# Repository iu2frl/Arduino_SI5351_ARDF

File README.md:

# Arduino_SI5351_ARDF
Remix of the Wobbit board by IARU R1, built at 9A22YOTA camp

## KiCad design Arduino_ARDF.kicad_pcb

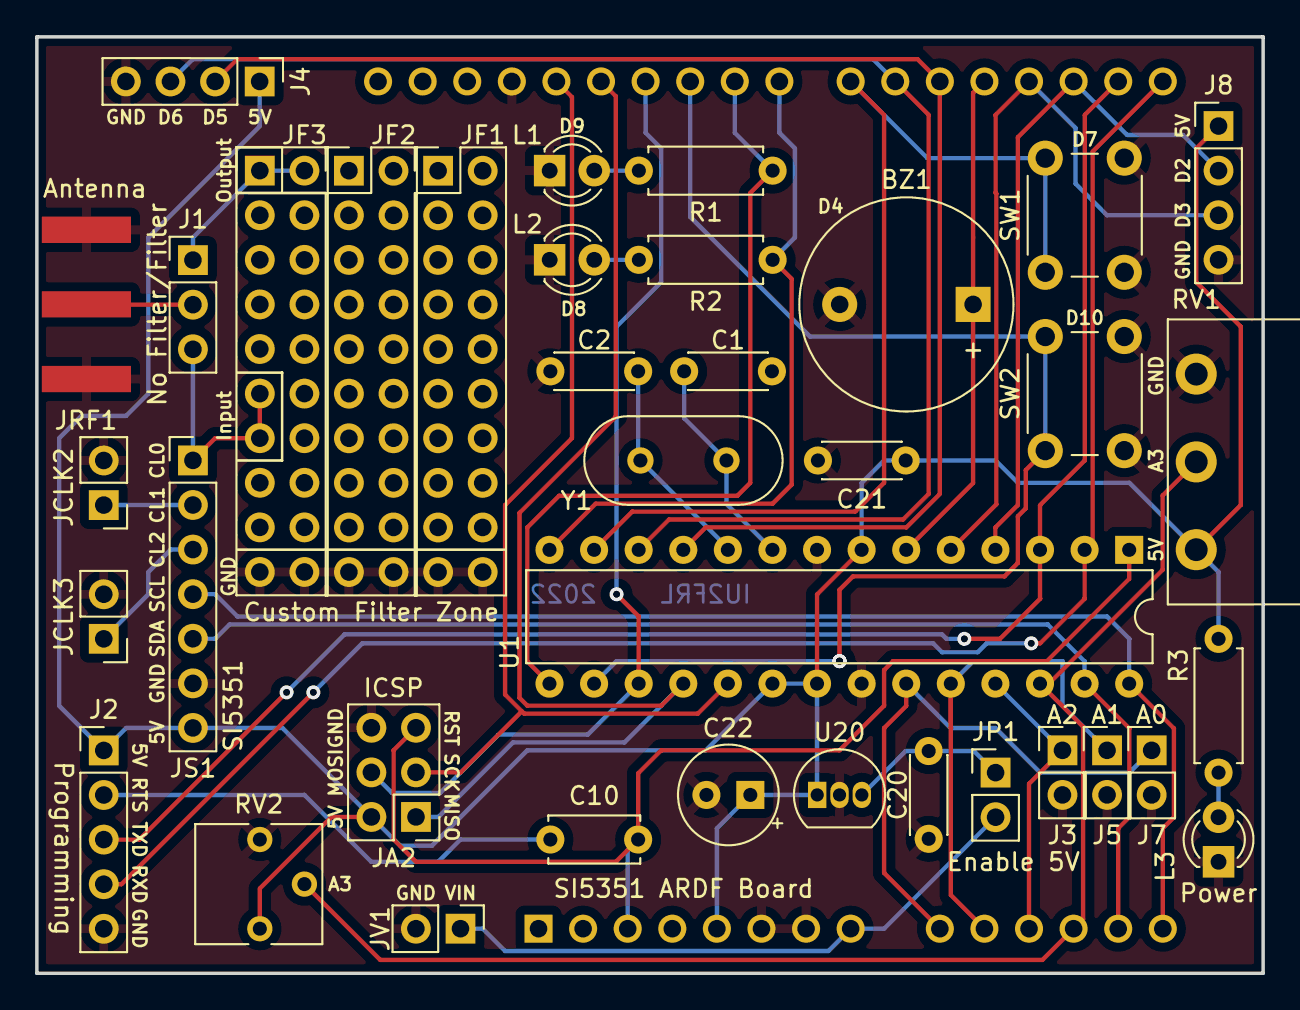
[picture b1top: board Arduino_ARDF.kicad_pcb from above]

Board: 2 copper layers, 69.8 x 53.3 mm, 38 parts (1 on the bottom side), 36 nets.

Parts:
BZ1: Buzzer; Buzzer_12x9.5RM7.6
C1, C2: 18p; C_Disc_D4.3mm_W1.9mm_P5.00mm
C10: 220n; C_Disc_D5.0mm_W2.5mm_P5.00mm
C20, C21: 100n; C_Disc_D4.3mm_W1.9mm_P5.00mm
C22: 47u; CP_Radial_Tantal_D5.5mm_P2.50mm
J1: Output Mode; PinHeader_1x03_P2.54mm_Vertical
J2: Programming; PinHeader_1x05_P2.54mm_Vertical
J3: Analog 2; PinHeader_1x02_P2.54mm_Vertical
J4: AUX2; PinHeader_1x04_P2.54mm_Vertical
J5: Analog 1; PinHeader_1x02_P2.54mm_Vertical
J7: Analog 0; PinHeader_1x02_P2.54mm_Vertical
J8: AUX1; PinHeader_1x04_P2.54mm_Vertical
JA1: Arduino_UNO_R3
JA2: ICSP; PinHeader_2x03_P2.54mm_Vertical
JCLK2: Clock 2; PinHeader_1x02_P2.54mm_Vertical
JCLK3: Clock 3; PinHeader_1x02_P2.54mm_Vertical
JF1: Filter 1; PinHeader_2x10_P2.54mm_Vertical
JF2: Filter 2; PinHeader_2x10_P2.54mm_Vertical
JF3: Filter 3; PinHeader_2x10_P2.54mm_Vertical
JP1: 5V EN; PinHeader_1x02_P2.54mm_Vertical
JRF1: OUT; SMA_Amphenol_132289_EdgeMount
JS1: SI5351 Board; PinHeader_1x07_P2.54mm_Vertical
JV1: Vin; PinHeader_1x02_P2.54mm_Vertical
L1, L2, L3: LED; LED_D3.0mm
R1, R2, R3: 470; R_Axial_DIN0207_L6.3mm_D2.5mm_P7.62mm_Horizontal
RV1: Potentiometer; Potentiometer_Piher_PC-16_Single_Horizontal
RV2: Potentiometer; Potentiometer_Vishay_T73YP_Vertical
SW1: Button 1; SW_PUSH_6mm
SW2: Button 2; SW_PUSH_6mm
U1: ATmega328-P; DIP-28_W7.62mm
U20: L78L05_TO92; TO-92_Inline
Y1: 16M; Crystal_HC18-U_Vertical

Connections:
+5V: C21.1, C22.1, J2.1, J4.1, J8.1, JA1.5 (+5V), JA2.2, JS1.7, R3.1, RV1.1, RV2.1, U1.7 (VCC), U1.20 (AVCC), U1.21 (AREF), U20.1 (VO)
A0: J7.1, JA1.9 (A0), U1.23 (PC0)
A1: J5.1, JA1.10 (A1), U1.24 (PC1)
A2: J3.1, JA1.11 (A2), U1.25 (PC2)
A3: JA1.12 (A3), RV1.2, RV2.2, U1.26 (PC3)
BUZ: BZ1.1 (-), JA1.19 (D4), U1.6 (PD4)
CLK0: J1.3, JF3.11, JF3.13, JS1.1
CLK1: JCLK2.1, JS1.2
CLK2: JCLK3.1, JS1.3
D2: J8.2, JA1.17 (D2), U1.4 (PD2)
D3: J8.3, JA1.18 (D3), U1.5 (PD3)
D5: J4.2, JA1.20 (D5), U1.11 (PD5)
D6: J4.3, JA1.21 (D6), U1.12 (PD6)
D7: JA1.22 (D7), SW1.1, U1.13 (PD7)
D10: JA1.25 (D10), SW2.1, U1.16 (PB2)
Filter: J1.1, JF3.1, JF3.2
GND: BZ1.2 (+), C1.1, C2.2, C20.2, C21.2, C22.2, J2.5, J3.2, J4.4, J5.2, J7.2, J8.4, JA1.6 (GND), JA1.7 (GND), JA1.29 (GND), JA2.6, JCLK2.2, JCLK3.2, JF1.19, JF1.20, JF2.19, JF2.20, JF3.19, JF3.20, JRF1.2 (Ext), JS1.6, JV1.2, L1.1 (K), L2.1 (K), L3.1 (K), RV1.3, RV2.3, SW1.2, SW2.2, U1.8 (GND), U1.22 (GND), U20.2 (GND)
LED1: JA1.24 (D9), R1.1, U1.15 (PB1)
LED2: JA1.23 (D8), R2.1, U1.14 (PB0)
MISO: JA1.27 (D12), JA2.1, U1.18 (PB4)
MOSI: JA1.26 (D11), JA2.4, U1.17 (PB3)
unnamed: C1.2, U1.9 (XTAL1/PB6), Y1.2
unnamed: C2.1, U1.10 (XTAL2/PB7), Y1.1
unnamed: C10.1, J2.2
unnamed: C20.1, JP1.1, U20.3 (VI)
unnamed: J1.2, JRF1.1 (In)
unnamed: L1.2 (A), R1.2
unnamed: L2.2 (A), R2.2
unnamed: L3.2 (A), R3.2
RST: C10.2, JA1.3 (~RESET), JA2.5, U1.1 (~RESET/PC6)
RXD: J2.4, JA1.15 (D0/RX), U1.2 (PD0)
SCK: JA1.28 (D13), JA2.3, U1.19 (PB5)
SCL: JA1.14 (SCL/A5), JS1.4, U1.28 (PC5)
SDA: JA1.13 (SDA/A4), JS1.5, U1.27 (PC4)
TXD: J2.3, JA1.16 (D1/TX), U1.3 (PD1)
VIN: JA1.8 (VIN), JP1.2, JV1.1

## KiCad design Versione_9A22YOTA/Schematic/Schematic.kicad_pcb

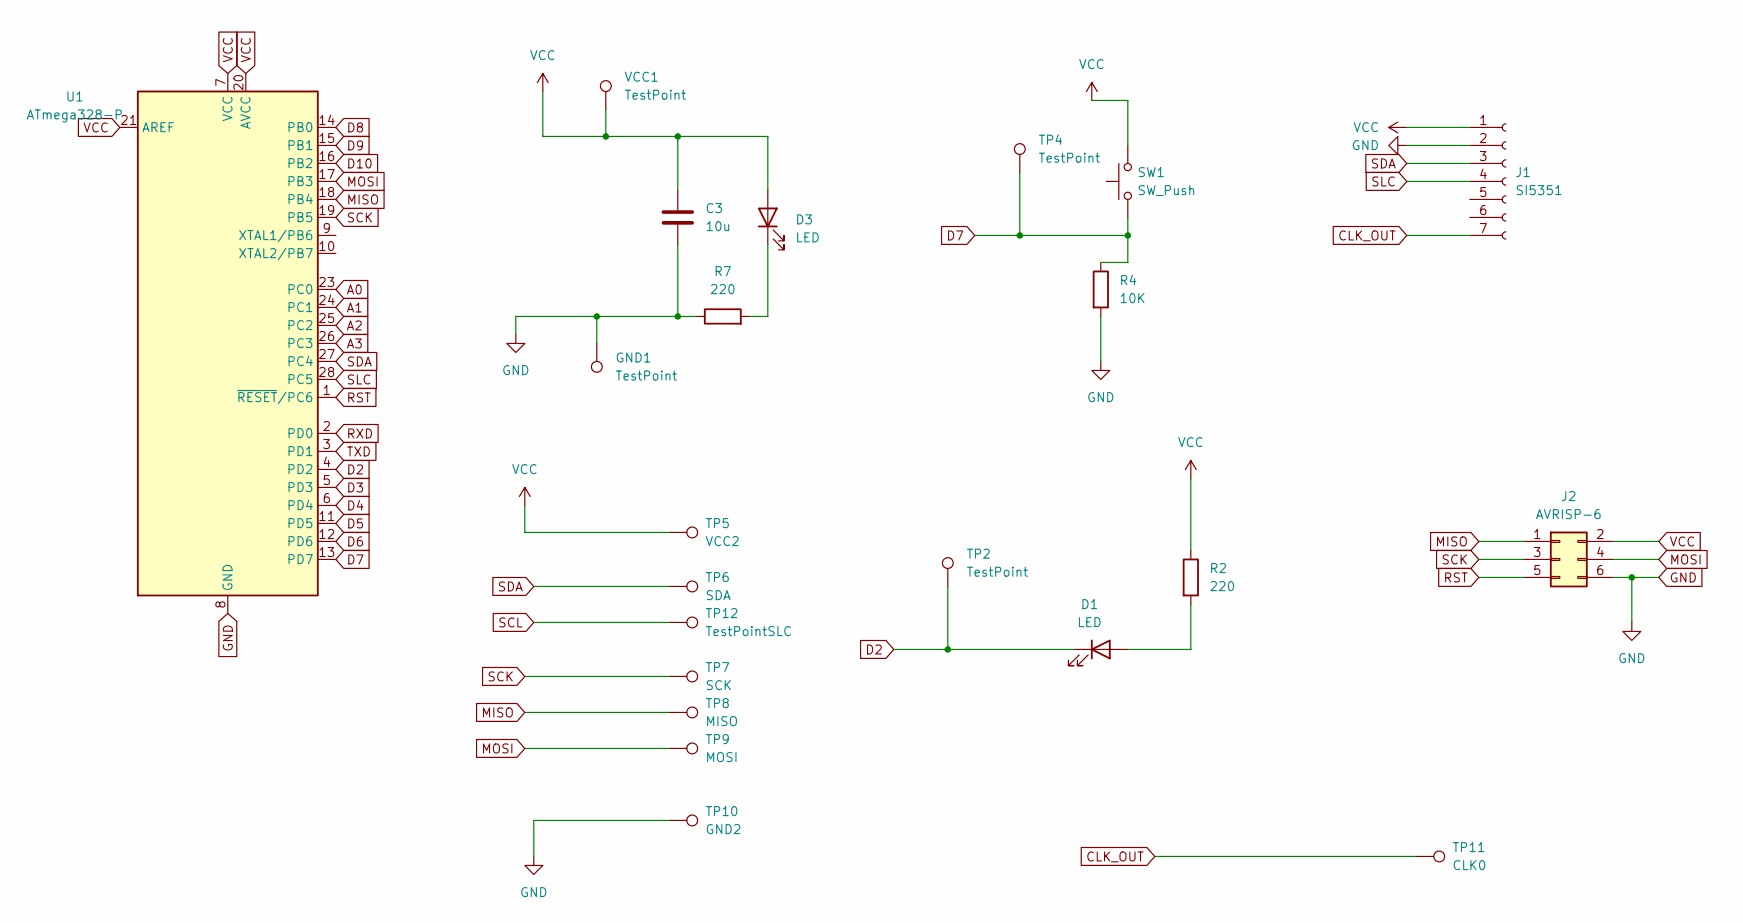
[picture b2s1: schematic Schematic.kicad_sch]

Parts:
C3: 10u; CP_Radial_D5.0mm_P2.00mm
D1, D3: LED; LED_D5.0mm
GND1: TestPoint; Pin_D1.0mm_L10.0mm
J1: SI5351; PinHeader_1x07_P2.54mm_Vertical
J2: AVRISP-6; PinHeader_2x03_P2.54mm_Vertical
R2, R7: 220; R_Axial_DIN0309_L9.0mm_D3.2mm_P12.70mm_Horizontal
R4: 10K; R_Axial_DIN0309_L9.0mm_D3.2mm_P12.70mm_Horizontal
SW1: SW_Push; SW_PUSH_6mm
TP2, TP4: TestPoint; Pin_D1.0mm_L10.0mm
TP5: VCC2; Pin_D1.0mm_L10.0mm
TP6: SDA; Pin_D1.0mm_L10.0mm
TP7: SCK; Pin_D1.0mm_L10.0mm
TP8: MISO; Pin_D1.0mm_L10.0mm
TP9: MOSI; Pin_D1.0mm_L10.0mm
TP10: GND2; Pin_D1.0mm_L10.0mm
TP11: CLK0; Pin_D1.0mm_L10.0mm
TP12: TestPointSLC; Pin_D1.0mm_L10.0mm
U1: ATmega328-P; DIP-28_W7.62mm
VCC1: TestPoint; Pin_D1.0mm_L10.0mm

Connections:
A0: U1.23 (PC0)
A1: U1.24 (PC1)
A2: U1.25 (PC2)
A3: U1.26 (PC3)
CLK_OUT: J1.7, TP11.1
D2: D1.1 (K), TP2.1, U1.4 (PD2)
D3: U1.5 (PD3)
D4: U1.6 (PD4)
D5: U1.11 (PD5)
D6: U1.12 (PD6)
D7: R4.1, SW1.1, TP4.1, U1.13 (PD7)
D8: U1.14 (PB0)
D9: U1.15 (PB1)
D10: U1.16 (PB2)
GND: C3.2, GND1.1, J1.2, J2.6, R4.2, R7.1, TP10.1, U1.8 (GND), U1.22 (GND)
MISO: J2.1, TP8.1, U1.18 (PB4)
MOSI: J2.4, TP9.1, U1.17 (PB3)
unnamed: D1.2 (A), R2.2
unnamed: D3.1 (K), R7.2
RST: J2.5, U1.1 (~RESET/PC6)
RXD: U1.2 (PD0)
SCK: J2.3, TP7.1, U1.19 (PB5)
SCL: TP12.1
SDA: J1.3, TP6.1, U1.27 (PC4)
SLC: J1.4, U1.28 (PC5)
TXD: U1.3 (PD1)
VCC: C3.1, D3.2 (A), J1.1, J2.2, R2.1, SW1.2, TP5.1, U1.7 (VCC), U1.20 (AVCC), U1.21 (AREF), VCC1.1

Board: 2 copper layers, 22 parts (0 on the bottom side), 13 nets, no tracks yet.

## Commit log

2022-08-20 Iniziato versione 9A22YOTA
2022-08-21 Iniziato PCB
2022-08-21 Ricominciato PCB
2022-08-22 Added workflow
2022-08-22 Finished PCB
